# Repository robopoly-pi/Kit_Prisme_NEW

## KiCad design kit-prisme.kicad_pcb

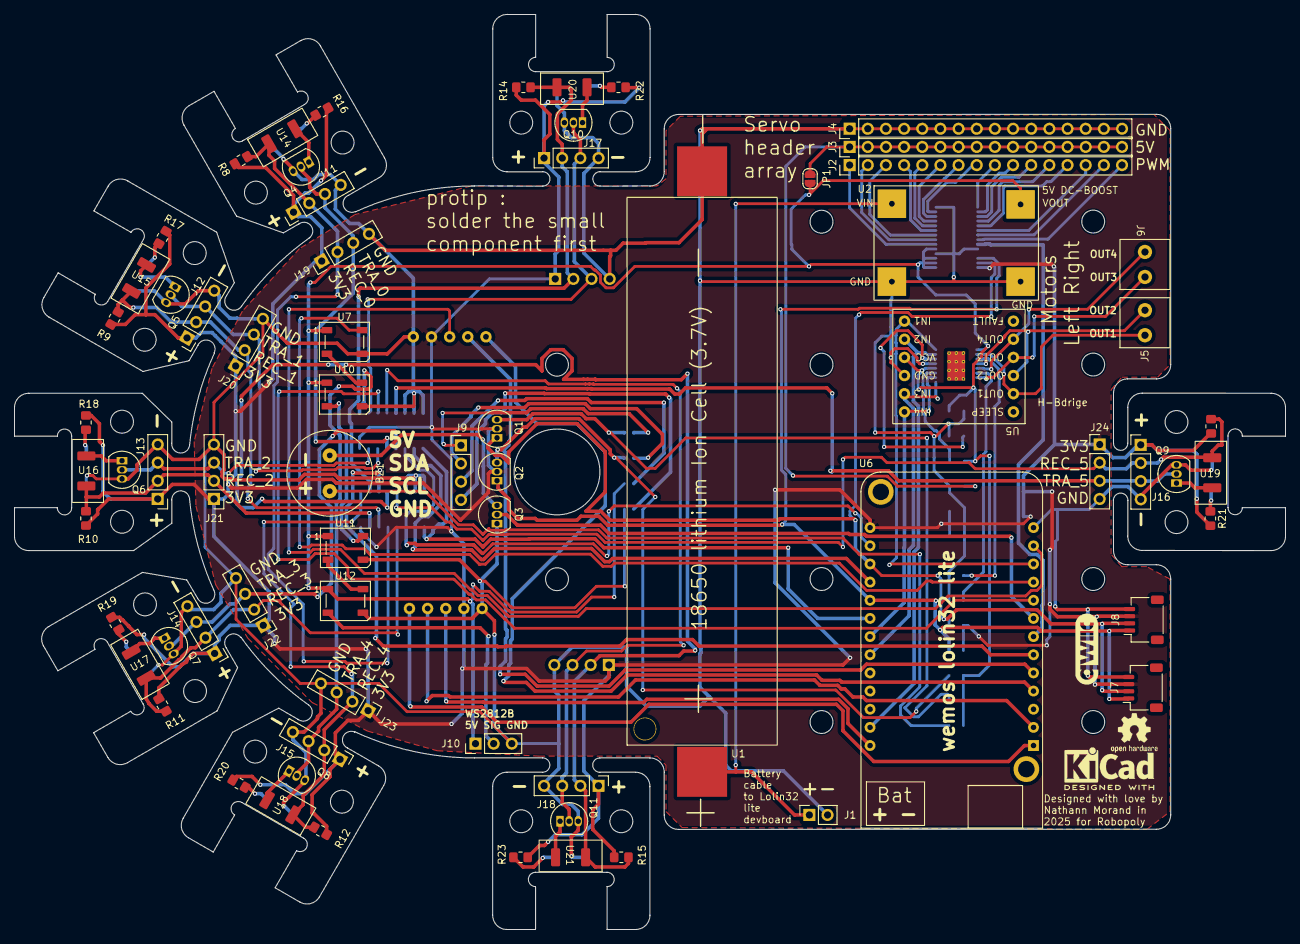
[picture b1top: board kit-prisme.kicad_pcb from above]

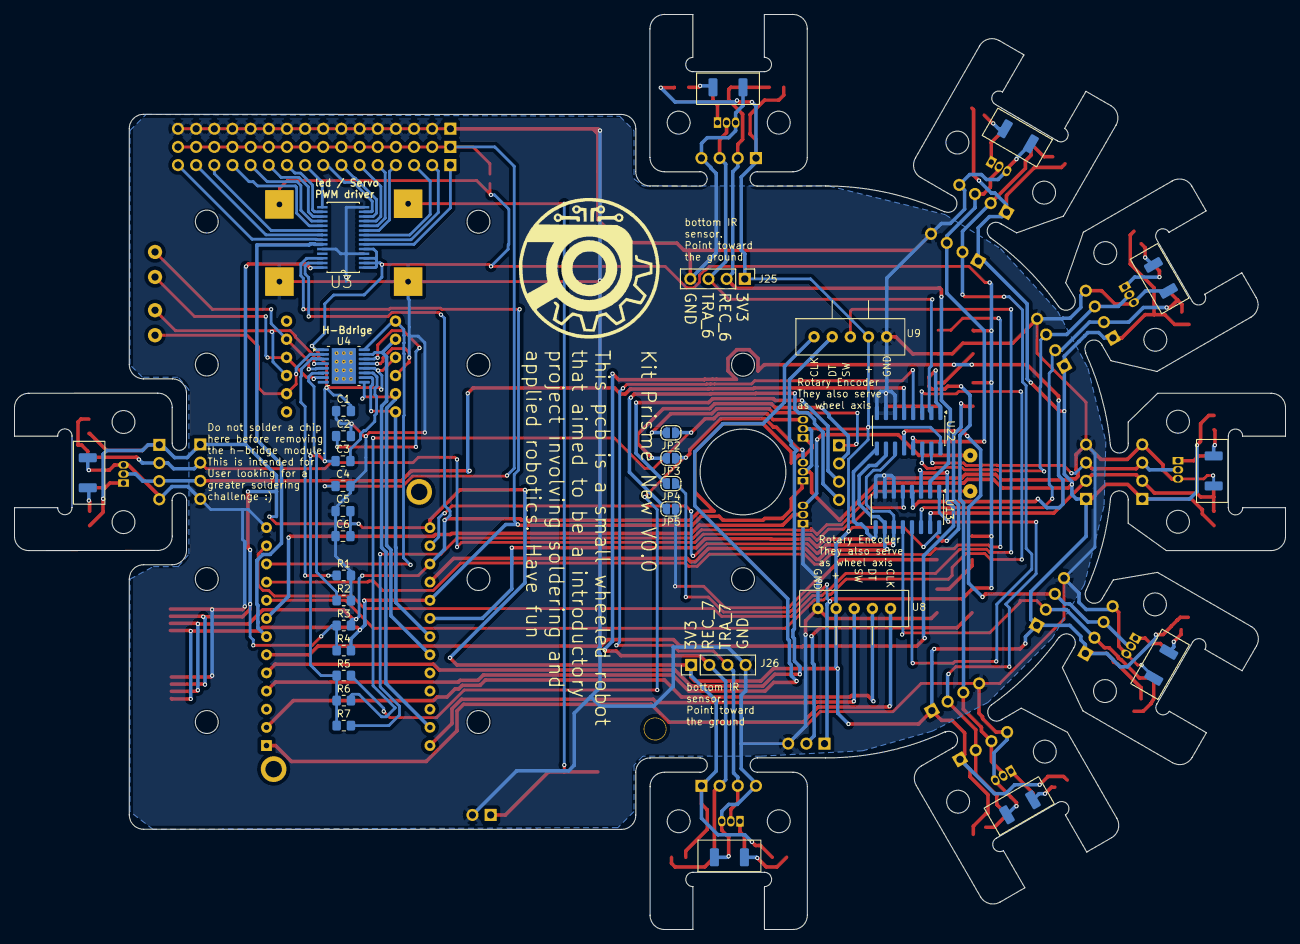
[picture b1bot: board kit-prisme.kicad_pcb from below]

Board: 2 copper layers, 177.8 x 128.0 mm, 94 parts (25 on the bottom side), 93 nets.

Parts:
BZ1: Buzzer; Buzzer_12mm_diam_5mm_pitch
C1, C4: 10 uF; C_0805_2012Metric_Pad1.18x1.45mm_HandSolder
C2: 2.2uF; C_0805_2012Metric_Pad1.18x1.45mm_HandSolder
C3, C5, C6: 10 nF; C_0805_2012Metric_Pad1.18x1.45mm_HandSolder
J1: Conn_01x02; PinSocket_1x02_P2.54mm_Vertical
J2, J3, J4: Conn_01x16; PinHeader_1x16_P2.54mm_Vertical
J5, J6: Conn_01x02; Bornier
J7, J8: Conn_01x04; JST_SH_SM04B-SRSS-TB_1x04-1MP_P1.00mm_Horizontal
J9, J11, J12, J13, J14, J15, J16, J17, J18, J19, J20, J21, J22, J23, J24, J25, J26: Conn_01x04; PinHeader_1x04_P2.54mm_Vertical
J10: Conn_01x03; PinHeader_1x03_P2.54mm_Vertical
JP1, JP2, JP3, JP4, JP5: SolderJumper_2_Bridged; SolderJumper-2_P1.3mm_Open_RoundedPad1.0x1.5mm
Q1, Q2, Q3, Q4, Q5, Q6, Q7, Q8, Q9, Q10, Q11: 2N7000; TO-92_Inline
R1, R2: 0R; R_0805_2012Metric_Pad1.20x1.40mm_HandSolder
R3, R4, R5, R6, R7, R8, R9, R10, R11, R12, R13, R14, R15, R16, R17, R18, R19, R20, R21, R22, R23: R; R_0805_2012Metric_Pad1.20x1.40mm_HandSolder
U1: Battery_Holder_18650_robop
U2: HW-668
U3: SOP65P640X110-28N
U4: HTSSOP-16-1EP_4.4x5mm_P0.65mm_EP3.4x5mm_Mask2.46x2.31mm_The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
U5: HW-627_DRV8833
U6: WEMOS_LoLin32_Lite
U7, U10, U11, U12: LED_WS2812B_PLCC4_5.0x5.0mm_P3.2mm
U8, U9: encoder
U13, U22: SOIC-16_3.9x9.9mm_P1.27mm
U14, U15, U16, U17, U18, U19, U20, U21: ITR_9909_Horizontal

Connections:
+3V3: C5.2, C6.2, J7.3, J8.3, J11.1, J12.1, J13.1, J14.1, J15.1, J16.1, J17.1, J18.1, J19.1, J20.1, J21.1, J22.1, J23.1, J24.1, J25.1, J26.1, Q1.2 (G), Q2.2 (G), R3.1, R4.1, R8.1, R9.1, R10.1, R11.1, R12.1, R13.1, R14.1, R15.1, R16.2, R17.2, R18.2, R19.2, R20.2, R21.2, R22.2, R23.2, U3.28 (VDD), U6.14 (3V3), U8.C, U9.C, U13.16 (VCC), U22.16 (VCC)
+3V8: J1.1, U1.1 (V_BAT), U2.1 (VIN)
+5V: C1.2, C3.1, J10.1, JP1.1 (A), JP4.1 (A), R5.1, R6.1, R7.1, U2.4 (OUT), U3.1 (A0), U3.2 (A1), U3.3 (A2), U3.5 (A4), U4.1 (nSLEEP), U4.12 (VM), U5.9 (VCC), U7.1 (VDD), U10.1 (VDD), U11.1 (VDD), U12.1 (VDD)
A1: U4.16 (AIN1), U5.7 (IN1/AIN1), U6.11 (IO14)
A2: U4.15 (AIN2), U5.8 (IN2/AIN2), U6.25 (IO15)
B1: U4.9 (BIN1), U5.11 (IN3/BIN1), U6.21 (IO16)
B2: U4.10 (BIN2), U5.12 (IN4/BIN2), U6.20 (IO17)
BUZZER: Q3.2 (G), U6.8 (IO25)
GND: C1.1, C2.2, C4.2, C5.1, C6.1, J1.2, J4.1, J4.2, J4.3, J4.4, J4.5, J4.6, J4.7, J4.8, J4.9, J4.10, J4.11, J4.12, J4.13, J4.14, J4.15, J4.16, J7.4, J8.4, J10.3, J11.4, J12.4, J13.4, J14.4, J15.4, J16.4, J17.4, J18.4, J19.4, J20.4, J21.4, J22.4, J23.4, J24.4, J25.4, J26.4, JP5.1 (A), Q3.1 (S), Q4.3 (D), Q5.3 (D), Q6.3 (D), Q7.3 (D), Q8.3 (D), Q9.3 (D), Q10.3 (D), Q11.3 (D), R1.2, R2.2, U1.2 (GND), U2.2 (GND), U2.3 (GND), U3.4 (A3), U3.14 (VSS), U3.24 (A5), U4.13 (GND), U5.10 (GND), U6.13 (GND), U7.3 (VSS), U8.S2, U9.S2, U10.3 (VSS), U11.3 (VSS), U12.3 (VSS), U13.6 (~E), U13.7 (VEE), U13.8 (GND), U14.3, U15.3, U16.3, U17.3, U18.3, U19.3, U20.3, U21.3, U22.6 (~E), U22.7 (VEE), U22.8 (GND)
IR_MODULATION: U6.9 (IO26), U22.3 (A)
IR_REC_0: J11.2, J19.2, R8.2, U13.13 (A0), U14.4
IR_REC_1: J12.2, J20.2, R9.2, U13.14 (A1), U15.4
IR_REC_2: J13.2, J21.2, R10.2, U13.15 (A2), U16.4
IR_REC_3: J14.2, J22.2, R11.2, U13.12 (A3), U17.4
IR_REC_4: J15.2, J23.2, R12.2, U13.1 (A4), U18.4
IR_REC_5: J16.2, J24.2, R13.2, U13.5 (A5), U19.4
IR_REC_6: J17.2, J25.2, R14.2, U13.2 (A6), U20.4
IR_REC_7: J18.2, J26.2, R15.2, U13.4 (A7), U21.4
IR_S0: U6.15 (IO22), U13.11 (S0), U22.11 (S0)
IR_S1: U6.17 (IO23), U13.10 (S1), U22.10 (S1)
IR_S2: U6.19 (IO5), U13.9 (S2), U22.9 (S2)
IR_TRA_0: J11.3, J19.3, Q4.2 (G), U22.13 (A0)
IR_TRA_1: J12.3, J20.3, Q5.2 (G), U22.14 (A1)
IR_TRA_2: J13.3, J21.3, Q6.2 (G), U22.15 (A2)
IR_TRA_3: J14.3, J22.3, Q7.2 (G), U22.12 (A3)
IR_TRA_4: J15.3, J23.3, Q8.2 (G), U22.1 (A4)
IR_TRA_5: J16.3, J24.3, Q9.2 (G), U22.5 (A5)
IR_TRA_6: J17.3, J25.3, Q10.2 (G), U22.2 (A6)
IR_TRA_7: J18.3, J26.3, Q11.2 (G), U22.4 (A7)
IR_analog: U6.6 (IO32), U13.3 (A)
unnamed: BZ1.1 (+), R7.2
unnamed: BZ1.2 (-), Q3.3 (D)
unnamed: J2.1, U3.6 (LED0)
unnamed: J2.2, U3.7 (LED1)
unnamed: J2.3, U3.8 (LED2)
unnamed: J2.4, U3.9 (LED3)
unnamed: J2.5, U3.10 (LED4)
unnamed: J2.6, U3.11 (LED5)
unnamed: J2.7, U3.12 (LED6)
unnamed: J2.8, U3.13 (LED7)
unnamed: J2.9, U3.15 (LED8)
unnamed: J2.10, U3.16 (LED9)
unnamed: J2.11, U3.17 (LED10)
unnamed: J2.12, U3.18 (LED11)
unnamed: J2.13, U3.19 (LED12)
unnamed: J2.14, U3.20 (LED13)
unnamed: J2.15, U3.21 (LED14)
unnamed: J2.16, U3.22 (LED15)
unnamed: C4.1, J3.1, J3.2, J3.3, J3.4, J3.5, J3.6, J3.7, J3.8, J3.9, J3.10, J3.11, J3.12, J3.13, J3.14, J3.15, J3.16, JP1.2 (B)
unnamed: J5.1, U4.2 (AOUT1), U5.2 (AOUT1/OUT1)
unnamed: J5.2, U4.4 (AOUT2), U5.3 (AOUT2/OUT2)
unnamed: J6.1, U4.7 (BOUT1), U5.4 (BOUT1/OUT3)
unnamed: J6.2, U4.5 (BOUT2), U5.5 (BOUT2/OUT4)
unnamed: J9.1, JP2.2 (B)
unnamed: J9.2, JP3.2 (B)
unnamed: J9.3, JP4.2 (B)
unnamed: J9.4, JP5.2 (B)
unnamed: J10.2, U12.2 (DOUT)
unnamed: JP2.1 (A), Q1.3 (D), R6.2
unnamed: JP3.1 (A), Q2.3 (D), R5.2
unnamed: Q4.1 (S), U14.1
unnamed: Q5.1 (S), U15.1
unnamed: Q6.1 (S), U16.1
unnamed: Q7.1 (S), U17.1
unnamed: Q8.1 (S), U18.1
unnamed: Q9.1 (S), U19.1
unnamed: Q10.1 (S), U20.1
unnamed: Q11.1 (S), U21.1
unnamed: R16.1, U14.2
unnamed: R17.1, U15.2
unnamed: R18.1, U16.2
unnamed: R19.1, U17.2
unnamed: R20.1, U18.2
unnamed: R21.1, U19.2
unnamed: R22.1, U20.2
unnamed: R23.1, U21.2
unnamed: R1.1, U4.3 (AISEN)
unnamed: R2.1, U4.6 (BISEN)
unnamed: C3.2, U4.11 (VCP)
unnamed: C2.1, U4.14 (VINT)
unnamed: U7.2 (DOUT), U10.4 (DIN)
unnamed: U10.2 (DOUT), U11.4 (DIN)
unnamed: U11.2 (DOUT), U12.4 (DIN)
PCA9685_OE: U3.23 (~OE), U6.7 (IO33)
RE_Left_A: U6.4 (I34), U9.A
RE_Left_B: U6.5 (I35), U9.B
RE_Left_btn: U6.12 (IO12), U9.S1
RE_Right_A: U6.1 (VP/I36), U8.A
RE_Right_B: U6.2 (VN/I39), U8.B
RE_Right_btn: U6.26 (IO13), U8.S1
SCL: J7.1, J8.1, Q2.1 (S), R4.2, U3.26 (SCL), U6.18 (IO18)
SDA: J7.2, J8.2, Q1.1 (S), R3.2, U3.27 (SDA), U6.16 (IO19)
WS2812_DIN: U6.10 (IO27), U7.4 (DIN)

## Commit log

2025-11-12 Initial commit of KiCad project
2025-11-12 Add .gitignore for KiCad
2025-11-12 Added action to compile PDF from schematic + layout
2025-11-13 Specify layers in PCB PDF export command
    Updated PDF export command to specify layers for PCB files.
2025-11-13 schematic improvment + exluded backup folder from git
2025-11-15 assigned footprint to each component, ready to route
2025-11-15 Auto-export KiCad PDFs
2025-11-17 looking for a good PCB layout
2025-11-18 layout is almost ready
2025-11-18 fine tuning layout
2025-11-24 updated some footprint + finnished rough layout
    now its a matter of cleanly laying out the silkscreen, label, move a bit the footprint to avoid collision but rough outline is good.
2025-11-25 redit bouard edge cut, shrinked a bit the board
2025-11-26 improved silkscreen
    added instruction and naming of component
2025-11-26 routed the PCB
2026-03-15 assembling test version, added issue / improvment
